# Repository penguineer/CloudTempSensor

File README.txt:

ESP-based Temperature Sensor with Cloud logging.

Uses https://github.com/jdunmire/kicad-ESP8266

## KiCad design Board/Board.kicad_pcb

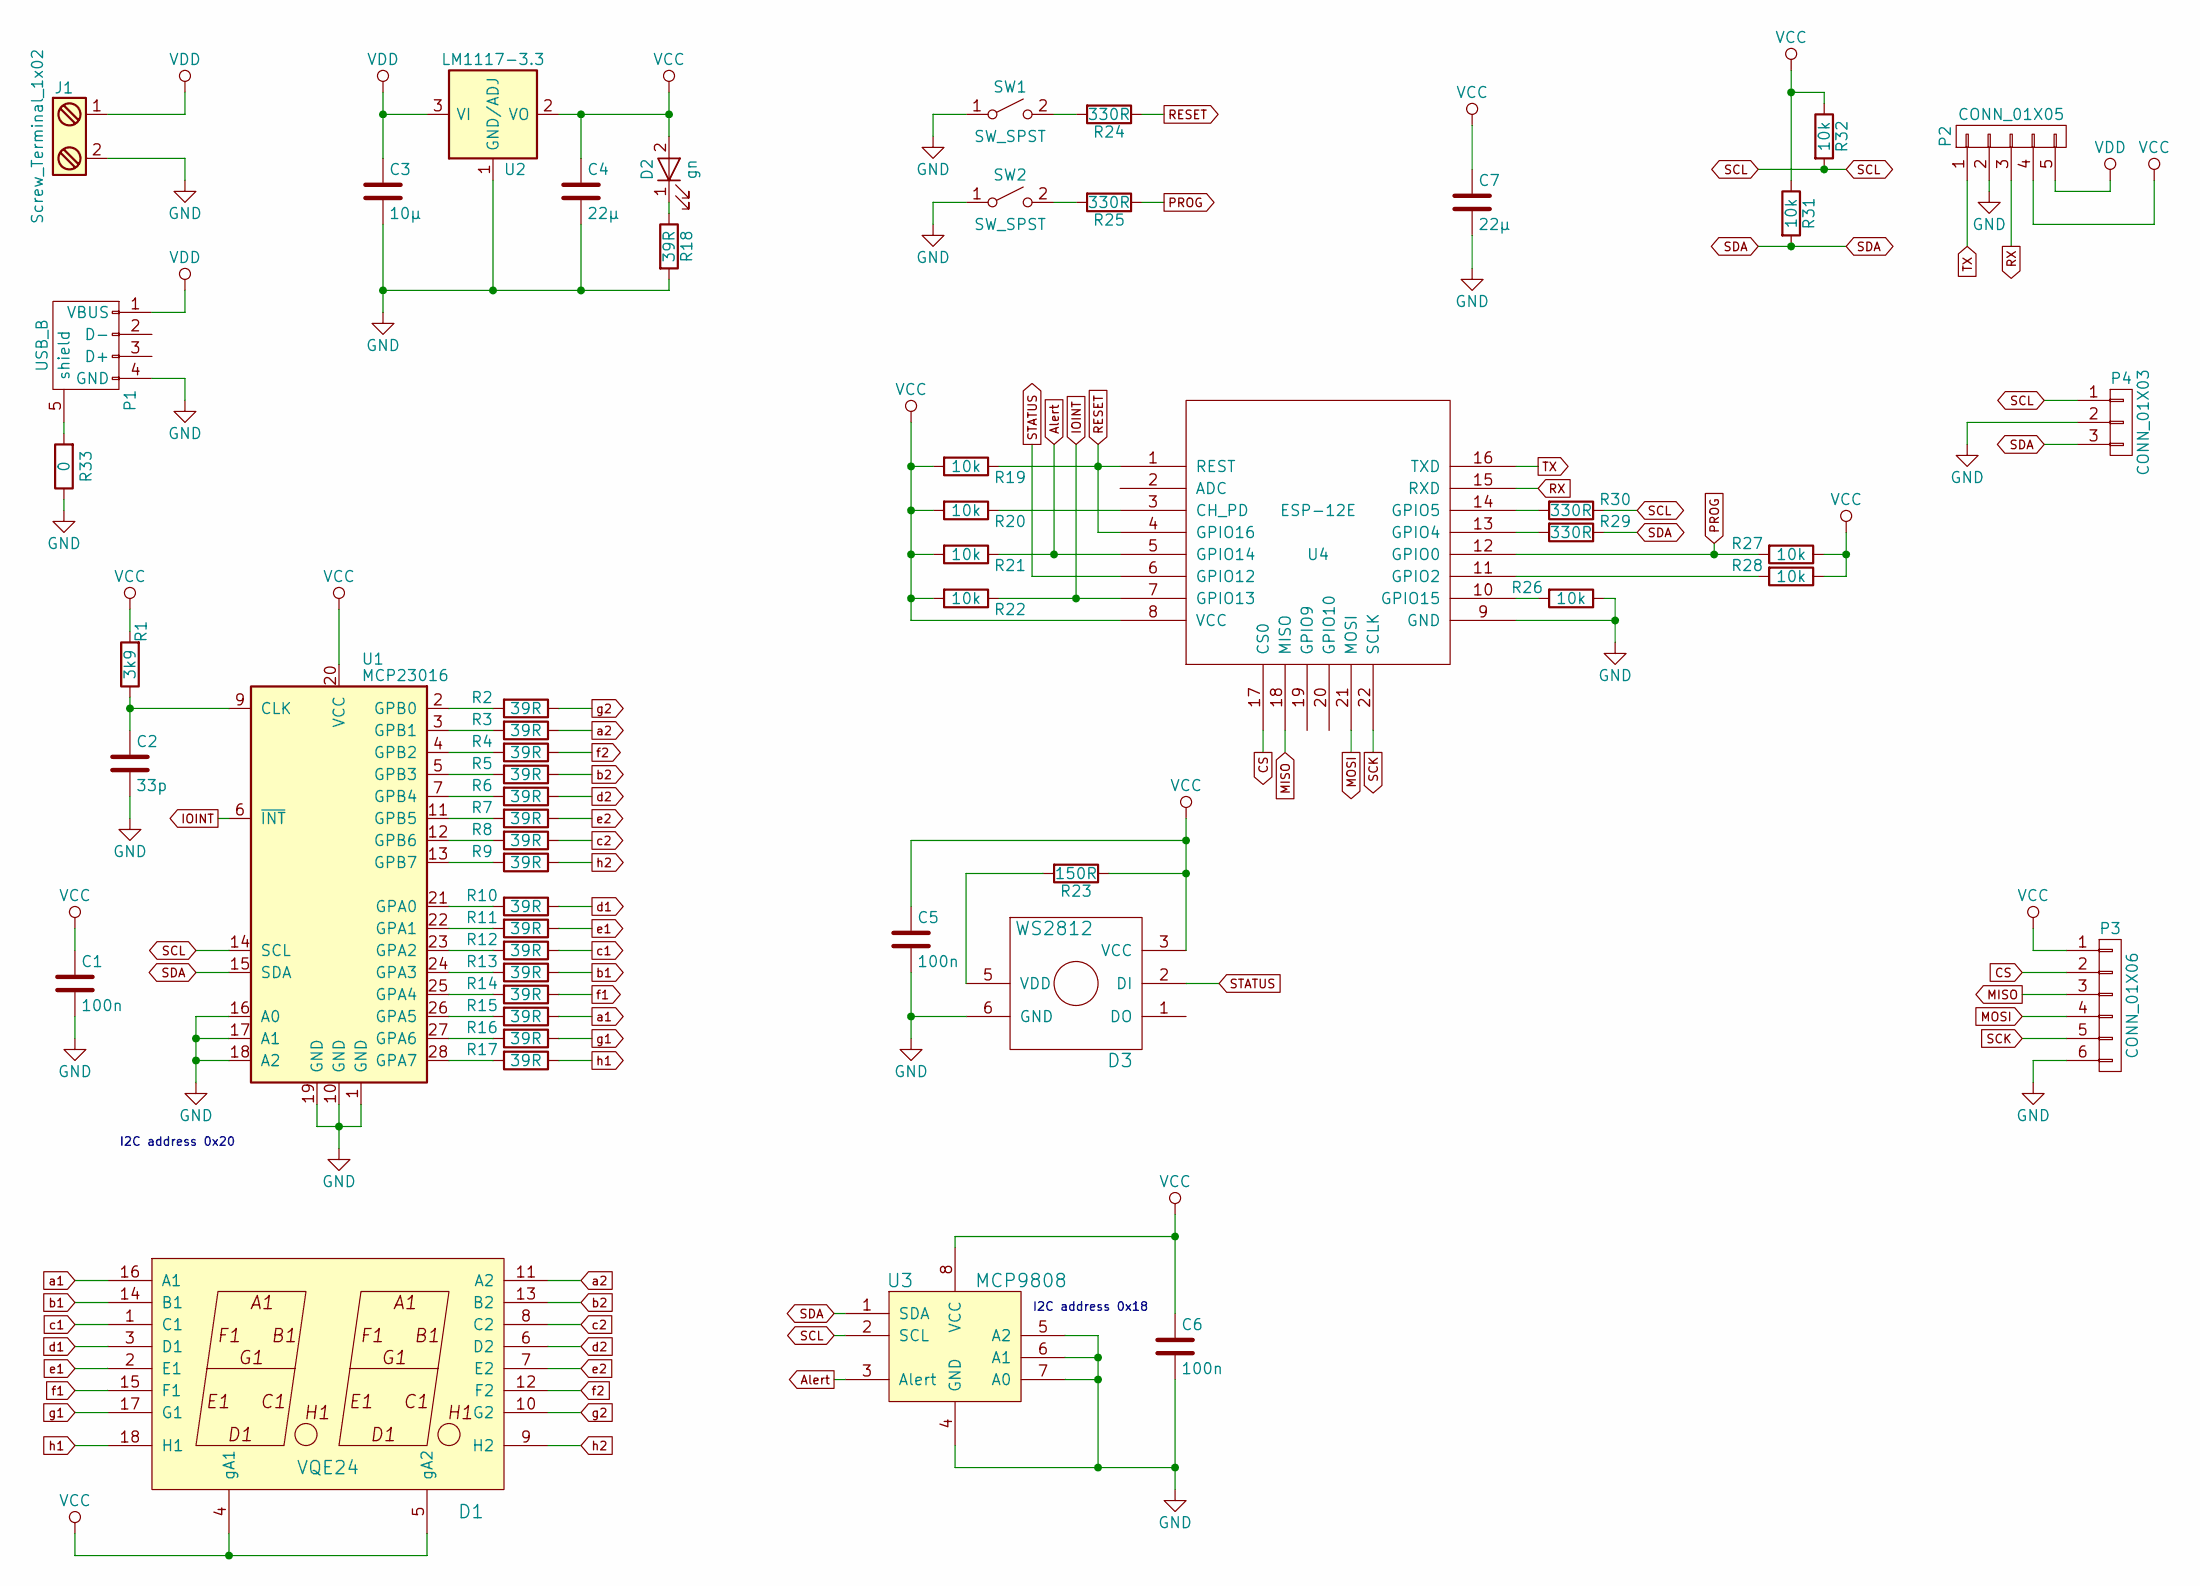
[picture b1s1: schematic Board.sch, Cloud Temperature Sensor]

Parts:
C1, C5, C6: 100n; C_0603_HandSoldering
C2: 33p; C_0603_HandSoldering
C3: 10µ; C_1206_HandSoldering
C4, C7: 22µ; C_1206_HandSoldering
D1: VQE24
D2: gn; LED_1206
D3: WS2812; LED_WS2812-PLCC6
J1: Screw_Terminal_1x02; AKL_101-02
P1: USB_B; USB_Micro-B
P2: CONN_01X05; Socket_Strip_Straight_1x05
P3: CONN_01X06; Socket_Strip_Straight_1x06
P4: CONN_01X03; Pin_Header_Straight_1x03
R1: 3k9; R_0603_HandSoldering
R2, R3, R4, R5, R6, R7, R8, R9, R10, R11, R12, R13, R14, R15, R16, R17, R18: 39R; R_0603_HandSoldering
R19, R20, R21, R22, R26, R27, R28, R31, R32: 10k; R_0603_HandSoldering
R23: 150R; R_0603_HandSoldering
R24, R25, R29, R30: 330R; R_0603_HandSoldering
R33: 0; R_0603_HandSoldering
SW1, SW2: SW_SPST; SW_SPST_EVQPE1
U1: MCP23016; SOIC-28W_7.5x17.9mm_Pitch1.27mm
U2: LM1117-3.3; SOT-223
U3: MCP9808; MSOP-8_3x3mm_Pitch0.65mm
U4: ESP-12E

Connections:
Alert: R21.1, U3.3 (Alert), U4.5 (GPIO14)
CS: P3.2, U4.17 (CS0)
GND: C1.2, C2.2, C3.2, C4.2, C5.2, C6.2, C7.2, D3.6 (GND), J1.2, P1.4 (GND), P2.2, P3.6, P4.2, R18.2, R26.1, R33.1, SW1.1 (A), SW2.1 (A), U1.1 (GND), U1.10 (GND), U1.16 (A0), U1.17 (A1), U1.18 (A2), U1.19 (GND), U2.1 (GND/ADJ), U3.4 (GND), U3.5 (A2), U3.6 (A1), U3.7 (A0), U4.9 (GND)
IOINT: R22.1, U1.6 (~INT), U4.7 (GPIO13)
MISO: P3.3, U4.18 (MISO)
MOSI: P3.4, U4.21 (MOSI)
unnamed: C2.1, R1.1, U1.9 (CLK)
unnamed: D2.1 (K), R18.1
unnamed: D3.5 (VDD), R23.2
unnamed: P1.5 (shield), R33.2
unnamed: R2.2, U1.2 (GPB0)
unnamed: R3.2, U1.3 (GPB1)
unnamed: R4.2, U1.4 (GPB2)
unnamed: R5.2, U1.5 (GPB3)
unnamed: R6.2, U1.7 (GPB4)
unnamed: R7.2, U1.11 (GPB5)
unnamed: R8.2, U1.12 (GPB6)
unnamed: R9.2, U1.13 (GPB7)
unnamed: R10.2, U1.21 (GPA0)
unnamed: R11.2, U1.22 (GPA1)
unnamed: R12.2, U1.23 (GPA2)
unnamed: R13.2, U1.24 (GPA3)
unnamed: R14.2, U1.25 (GPA4)
unnamed: R15.2, U1.26 (GPA5)
unnamed: R16.2, U1.27 (GPA6)
unnamed: R17.2, U1.28 (GPA7)
unnamed: R20.1, U4.3 (CH_PD)
unnamed: R24.2, SW1.2 (B)
unnamed: R25.2, SW2.2 (B)
unnamed: R26.2, U4.10 (GPIO15)
unnamed: R28.2, U4.11 (GPIO2)
unnamed: R29.2, U4.13 (GPIO4)
unnamed: R30.2, U4.14 (GPIO5)
PROG: R25.1, R27.2, U4.12 (GPIO0)
RESET: R19.1, R24.1, U4.1 (REST), U4.4 (GPIO16)
RX: P2.3, U4.15 (RXD)
SCK: P3.5, U4.22 (SCLK)
SCL: P4.1, R30.1, R32.2, U1.14 (SCL), U3.2 (SCL)
SDA: P4.3, R29.1, R31.2, U1.15 (SDA), U3.1 (SDA)
STATUS: D3.2 (DI), U4.6 (GPIO12)
TX: P2.1, U4.16 (TXD)
VCC: C1.1, C4.1, C5.1, C6.1, C7.1, D1.4 (gA1), D1.5 (gA2), D2.2 (A), D3.3 (VCC), P2.4, P3.1, R1.2, R19.2, R20.2, R21.2, R22.2, R23.1, R27.1, R28.1, R31.1, R32.1, U1.20 (VCC), U2.2 (VO), U2.4 (VO), U3.8 (VCC), U4.8 (VCC)
VDD: C3.1, J1.1, P1.1 (VBUS), P2.5, U2.3 (VI)
a1: D1.16 (A1), R15.1
a2: D1.11 (A2), R3.1
b1: D1.14 (B1), R13.1
b2: D1.13 (B2), R5.1
c1: D1.1 (C1), R12.1
c2: D1.8 (C2), R8.1
d1: D1.3 (D1), R10.1
d2: D1.6 (D2), R6.1
e1: D1.2 (E1), R11.1
e2: D1.7 (E2), R7.1
f1: D1.15 (F1), R14.1
f2: D1.12 (F2), R4.1
g1: D1.17 (G1), R16.1
g2: D1.10 (G2), R2.1
h1: D1.18 (H1), R17.1
h2: D1.9 (H2), R9.1

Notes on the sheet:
I2C address 0x18
I2C address 0x20

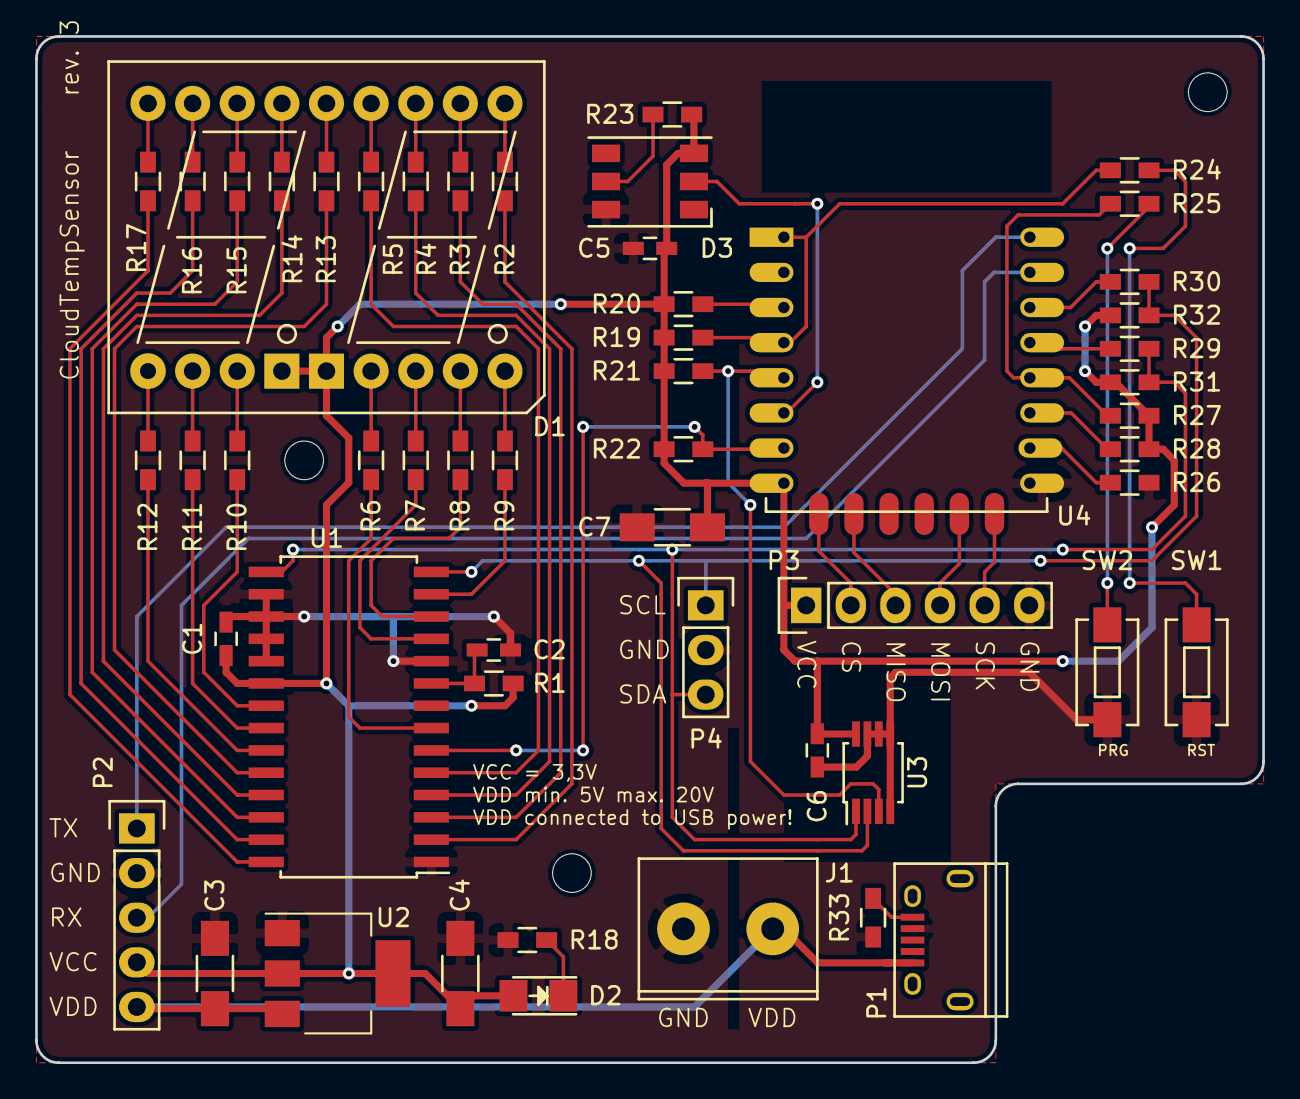
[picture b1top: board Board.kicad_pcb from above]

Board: 2 copper layers, 69.9 x 58.4 mm, 54 parts (0 on the bottom side), 59 nets.

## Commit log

2016-06-17 Initial commit.
2016-06-17 Initial firmware commit
2017-04-02 Next firmware revision: WIFI, MQTT, EEPROM config, MCP9808
2017-04-02 Organize temperature sensor functions
2017-04-02 Clean-up the connection failure handling
    Go to config mode, when connection cannot be established during setup, otherwise reboot the device if the connection has been lost.
2017-04-02 Be more concise aboout the MQTT server label
2017-04-02 Clean-up state LED naming and usage
    Only one state LED is left and the sybmols have consistent naming.
2017-04-03 Set EEPROM magic word during configuration
2017-04-03 Add timeout and some robustness to MQTT connection setup
2017-04-12 Read config from JSON via HTTP
2017-04-12 Add JSON config example
2017-04-12 Add HTTP authentication
2017-04-13 Add basic update routine
2017-04-13 Add Update UART command
2017-04-13 Add update URL to HTTP configuration
2017-04-13 Restart after Update
2017-04-13 Show software version on startup
2018-04-14 gitignore for kicad projects
2018-04-14 First go on schematic
    7-segment controller does not work out so nicely, better use
    a port expander like http://www.ti.com/product/tca9554
2018-04-14 Add kicad library link to Readme
2018-04-15 Schematic: 7segment display done
2018-04-15 Power supply
2018-04-15 Power and ESP environment
2018-04-15 Use MCP23016
2018-04-16 WS2812 for status and bypass for ESP
2018-04-16 Footprints and TODOs
2018-04-17 Schematic: final TODOs
2018-04-17 Schematic: Annotate symbols
2018-04-17 Add an SPI connector
2018-04-21 Move some things around in the schematic
2018-04-21 Remaining footprints
2018-04-27 Layout for power and 7 segment display
2018-04-27 Layout rev 1
2018-04-27 Final Rev 1
2018-04-27 Board as sent to DirtyPCB
2018-04-27 sent to dirtypcb
2018-07-02 Fix footprint for U1
2018-07-15 Board2 sent to DirtyPCBs
2018-08-26 Minimal adaptions for the board
2018-08-26 Add the display
2018-08-26 Board Revision 3: Thermal relief for the temp sensor
2018-08-26 I2C connector and more thermal decoupling
2018-09-24 Minor changes for rev3
2018-09-24 Board revision 3
